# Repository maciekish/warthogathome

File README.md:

# Warthog at Home

This is a compilation of various resources to build an A-10C II cockpit for home entertainment. It is loosely based on [The Warthog Project](http://thewarthogproject.com) and frame designs by Flim on the ED forums.

This project started out as an idea for 3d-printed panels for the F-GT Lite racing chair, but as time went on it became more and more obvious that it's just too small and i would have to make way too many compromises along the way. For this reason i decided to use some of the available resources online to build a proper cockpit, but still trying to keep it as "stowable" as possible by making it modular and not mounted to the floor.

## License

This project is licensed under the MIT License except as stated otherwise in certain parts not made by me.

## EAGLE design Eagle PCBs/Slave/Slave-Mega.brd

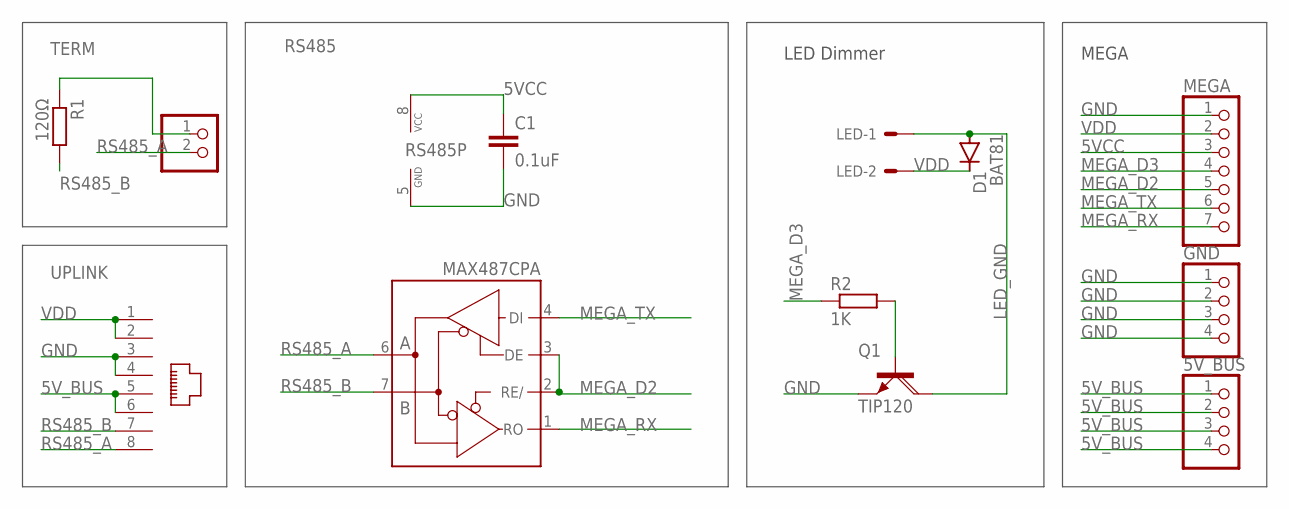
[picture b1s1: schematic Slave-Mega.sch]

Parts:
5V_BUS: PINHD-1X4; 1X04
C1: 0.1uF; C025-025X050
D1: BAT81; DO34-7
GND: PINHD-1X4; 1X04
LED: KK-156-2
MEGA: PINHD-1X7; 1X07
Q1: TIP120; TO220AH
R1: 120Ω; 0204/7
R2: 1K; 0207/10
RS485: MAX487CPA; DIL08
TERM: PINHD-1X2; 1X02
UPLINK: RJ45-8P8C

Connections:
5VCC: C1.1, MEGA.3, RS485.8 (VCC)
5V_BUS: 5V_BUS.1, 5V_BUS.2, 5V_BUS.3, 5V_BUS.4, UPLINK.5, UPLINK.6
GND: C1.2, GND.1, GND.2, GND.3, GND.4, MEGA.1, Q1.E, RS485.5 (GND), UPLINK.3, UPLINK.4
LED_GND: D1.A, LED.1, Q1.C
LED_PWM: Q1.B, R2.2
MEGA_D2: MEGA.5, RS485.2 (RE/), RS485.3 (DE)
MEGA_D3: MEGA.4, R2.1
MEGA_RX: MEGA.7, RS485.1 (RO)
MEGA_TX: MEGA.6, RS485.4 (DI)
RS485_A: RS485.6 (A), TERM.2, UPLINK.8
RS485_B: R1.2, RS485.7 (B), UPLINK.7
TERM: R1.1, TERM.1
VDD: D1.C, LED.2, MEGA.2, UPLINK.1, UPLINK.2

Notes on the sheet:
LED Dimmer
MEGA

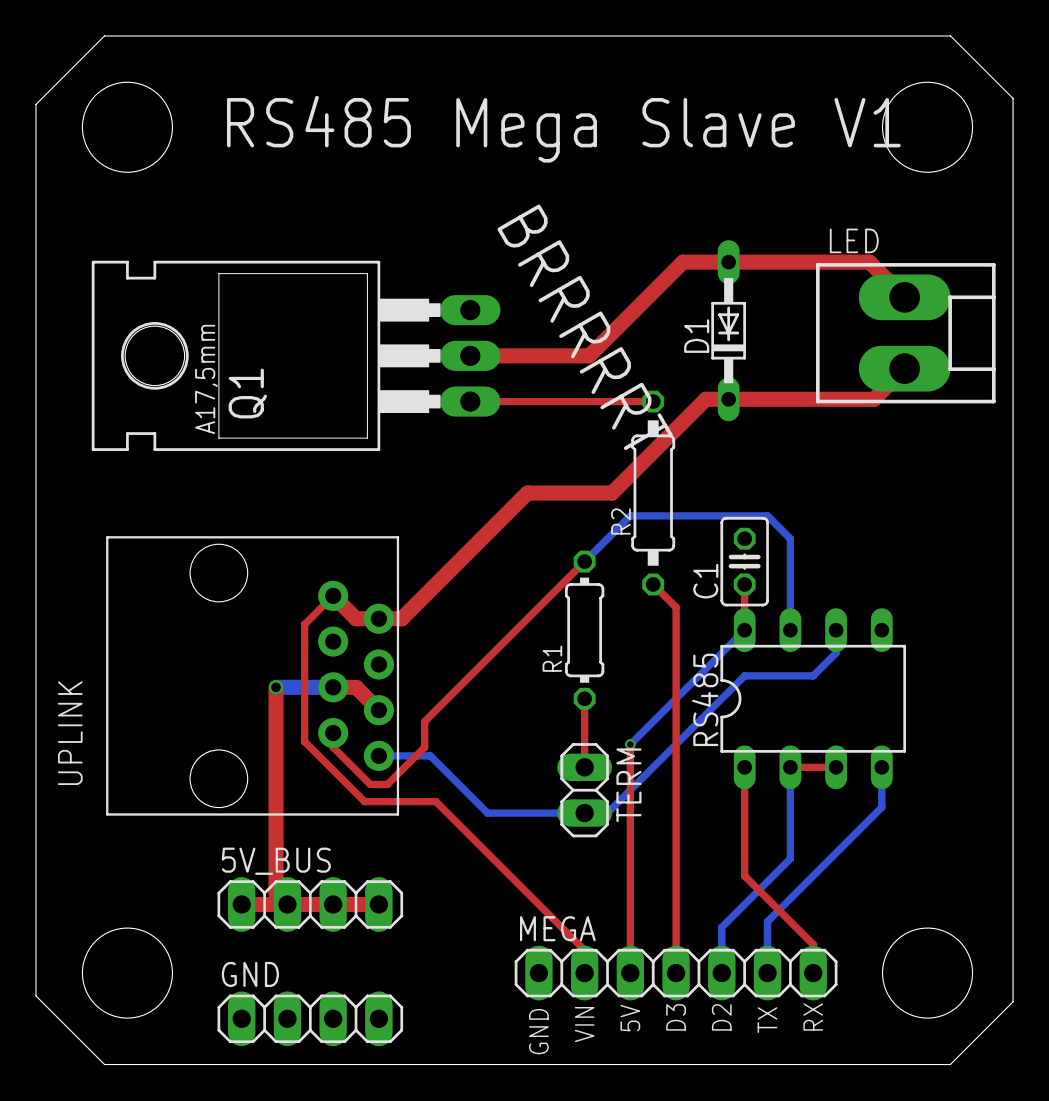
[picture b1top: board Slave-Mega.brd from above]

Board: 2 copper layers, 54.3 x 57.1 mm, 12 parts (0 on the bottom side), 13 nets.

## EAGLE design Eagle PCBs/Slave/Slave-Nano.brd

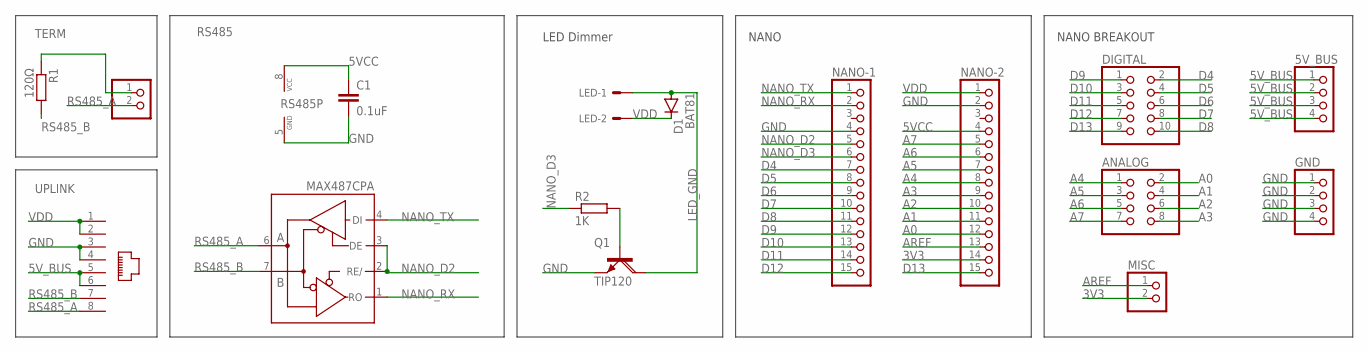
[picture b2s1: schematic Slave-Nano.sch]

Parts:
5V_BUS: PINHD-1X4; 1X04
ANALOG: PINHD-2X4; 2X04
C1: 0.1uF; C025-025X050
D1: BAT81; DO34-7
DIGITAL: PINHD-2X5; 2X05
GND: PINHD-1X4; 1X04
LED: KK-156-2
MISC: PINHD-1X2; 1X02
NANO-1, NANO-2: PINHD-1X15; 1X15
Q1: TIP120; TO220AH
R1: 120Ω; 0204/7
R2: 1K; 0204/7
RS485: MAX487CPA; DIL08
TERM: PINHD-1X2; 1X02
UPLINK: RJ45-8P8C

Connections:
3V3: MISC.2, NANO-2.14
5VCC: C1.1, NANO-2.4, RS485.8 (VCC)
5V_BUS: 5V_BUS.1, 5V_BUS.2, 5V_BUS.3, 5V_BUS.4, UPLINK.5, UPLINK.6
A0: ANALOG.2, NANO-2.12
A1: ANALOG.4, NANO-2.11
A2: ANALOG.6, NANO-2.10
A3: ANALOG.8, NANO-2.9
A4: ANALOG.1, NANO-2.8
A5: ANALOG.3, NANO-2.7
A6: ANALOG.5, NANO-2.6
A7: ANALOG.7, NANO-2.5
AREF: MISC.1, NANO-2.13
D4: DIGITAL.2, NANO-1.7
D5: DIGITAL.4, NANO-1.8
D6: DIGITAL.6, NANO-1.9
D7: DIGITAL.8, NANO-1.10
D8: DIGITAL.10, NANO-1.11
D9: DIGITAL.1, NANO-1.12
D10: DIGITAL.3, NANO-1.13
D11: DIGITAL.5, NANO-1.14
D12: DIGITAL.7, NANO-1.15
D13: DIGITAL.9, NANO-2.15
GND: C1.2, GND.1, GND.2, GND.3, GND.4, NANO-1.4, NANO-2.2, Q1.E, RS485.5 (GND), UPLINK.3, UPLINK.4
LED_GND: D1.A, LED.1, Q1.C
LED_PWM: Q1.B, R2.2
NANO_D2: NANO-1.5, RS485.2 (RE/), RS485.3 (DE)
NANO_D3: NANO-1.6, R2.1
NANO_RX: NANO-1.2, RS485.1 (RO)
NANO_TX: NANO-1.1, RS485.4 (DI)
RS485_A: RS485.6 (A), TERM.2, UPLINK.8
RS485_B: R1.2, RS485.7 (B), UPLINK.7
TERM: R1.1, TERM.1
VDD: D1.C, LED.2, NANO-2.1, UPLINK.1, UPLINK.2

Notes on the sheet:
LED Dimmer
NANO
NANO BREAKOUT

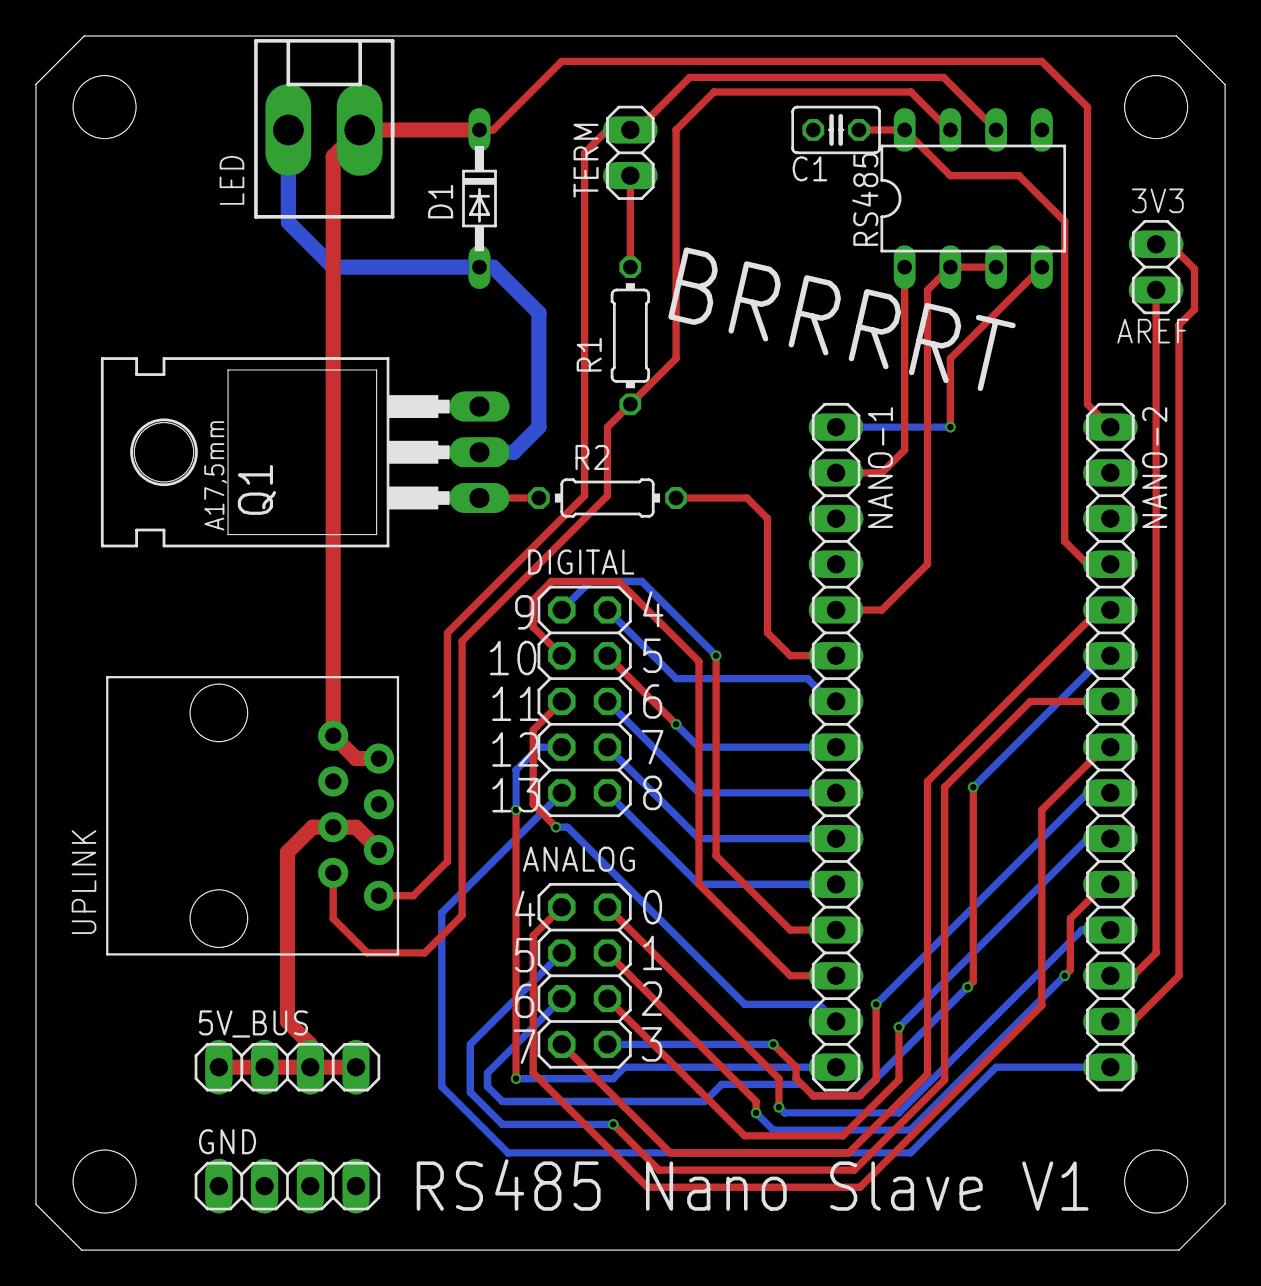
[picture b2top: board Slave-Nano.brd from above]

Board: 2 copper layers, 66.1 x 67.5 mm, 16 parts (0 on the bottom side), 33 nets.

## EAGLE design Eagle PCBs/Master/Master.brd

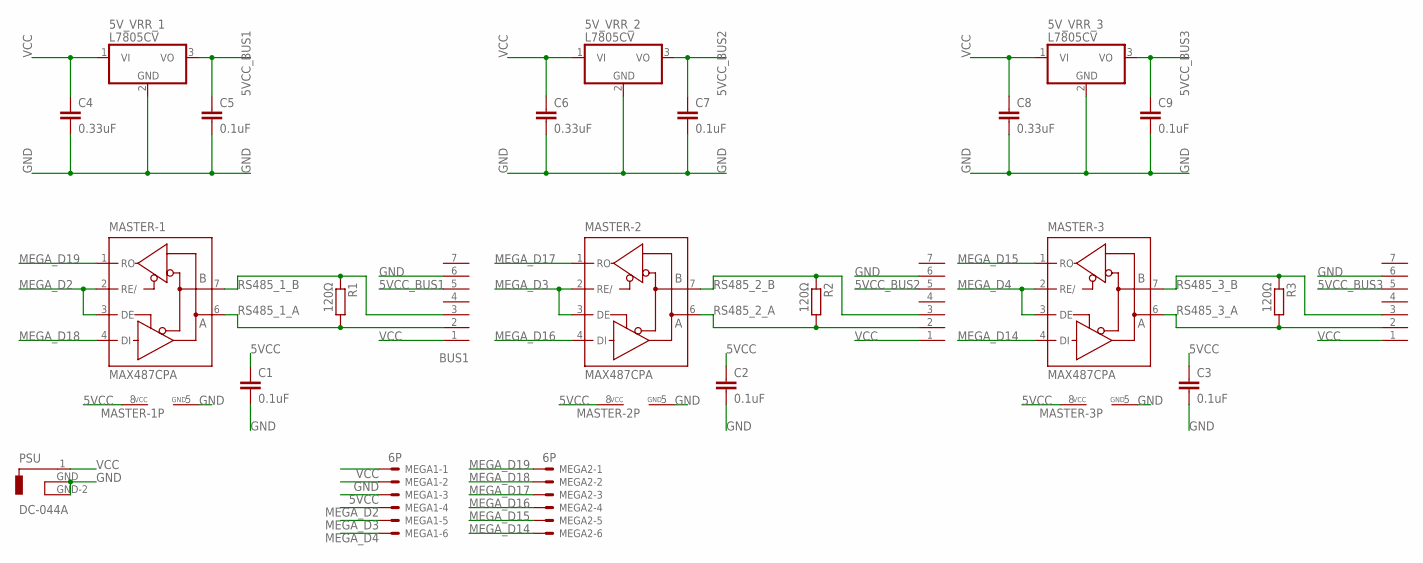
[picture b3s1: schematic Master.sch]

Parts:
5V_VRR_1, 5V_VRR_2, 5V_VRR_3: L7805CV; TO220H
BUS1, BUS2, BUS3: GX12-7P
C1, C2, C3, C5, C7, C9: 0.1uF; C025-025X050
C4, C6, C8: 0.33uF; C025-025X050
MASTER-1, MASTER-2, MASTER-3: MAX487CPA; DIL08
MEGA1, MEGA2: 6P; 22-23-2061
PSU: DC-044A
R1, R2, R3: 120Ω; 0207/10

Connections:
5VCC: C1.1, C2.1, C3.1, MASTER-1.8 (VCC), MASTER-2.8 (VCC), MASTER-3.8 (VCC), MEGA1.3
5VCC_BUS1: 5V_VRR_1.3 (VO), BUS1.5, C5.1
5VCC_BUS2: 5V_VRR_2.3 (VO), BUS2.5, C7.1
5VCC_BUS3: 5V_VRR_3.3 (VO), BUS3.5, C9.1
GND: 5V_VRR_1.2 (GND), 5V_VRR_2.2 (GND), 5V_VRR_3.2 (GND), BUS1.6, BUS2.6, BUS3.6, C1.2, C2.2, C3.2, C4.2, C5.2, C6.2, C7.2, C8.2, C9.2, MASTER-1.5 (GND), MASTER-2.5 (GND), MASTER-3.5 (GND), MEGA1.2, PSU.GND, PSU.GND-2
MEGA_D2: MASTER-1.2 (RE/), MASTER-1.3 (DE), MEGA1.4
MEGA_D3: MASTER-2.2 (RE/), MASTER-2.3 (DE), MEGA1.5
MEGA_D4: MASTER-3.2 (RE/), MASTER-3.3 (DE), MEGA1.6
MEGA_D14: MASTER-3.4 (DI), MEGA2.6
MEGA_D15: MASTER-3.1 (RO), MEGA2.5
MEGA_D16: MASTER-2.4 (DI), MEGA2.4
MEGA_D17: MASTER-2.1 (RO), MEGA2.3
MEGA_D18: MASTER-1.4 (DI), MEGA2.2
MEGA_D19: MASTER-1.1 (RO), MEGA2.1
RS485_1_A: BUS1.2, MASTER-1.6 (A), R1.2
RS485_1_B: BUS1.3, MASTER-1.7 (B), R1.1
RS485_2_A: BUS2.2, MASTER-2.6 (A), R2.2
RS485_2_B: BUS2.3, MASTER-2.7 (B), R2.1
RS485_3_A: BUS3.2, MASTER-3.6 (A), R3.2
RS485_3_B: BUS3.3, MASTER-3.7 (B), R3.1
VCC: 5V_VRR_1.1 (VI), 5V_VRR_2.1 (VI), 5V_VRR_3.1 (VI), BUS1.1, BUS2.1, BUS3.1, C4.1, C6.1, C8.1, MEGA1.1, PSU.1

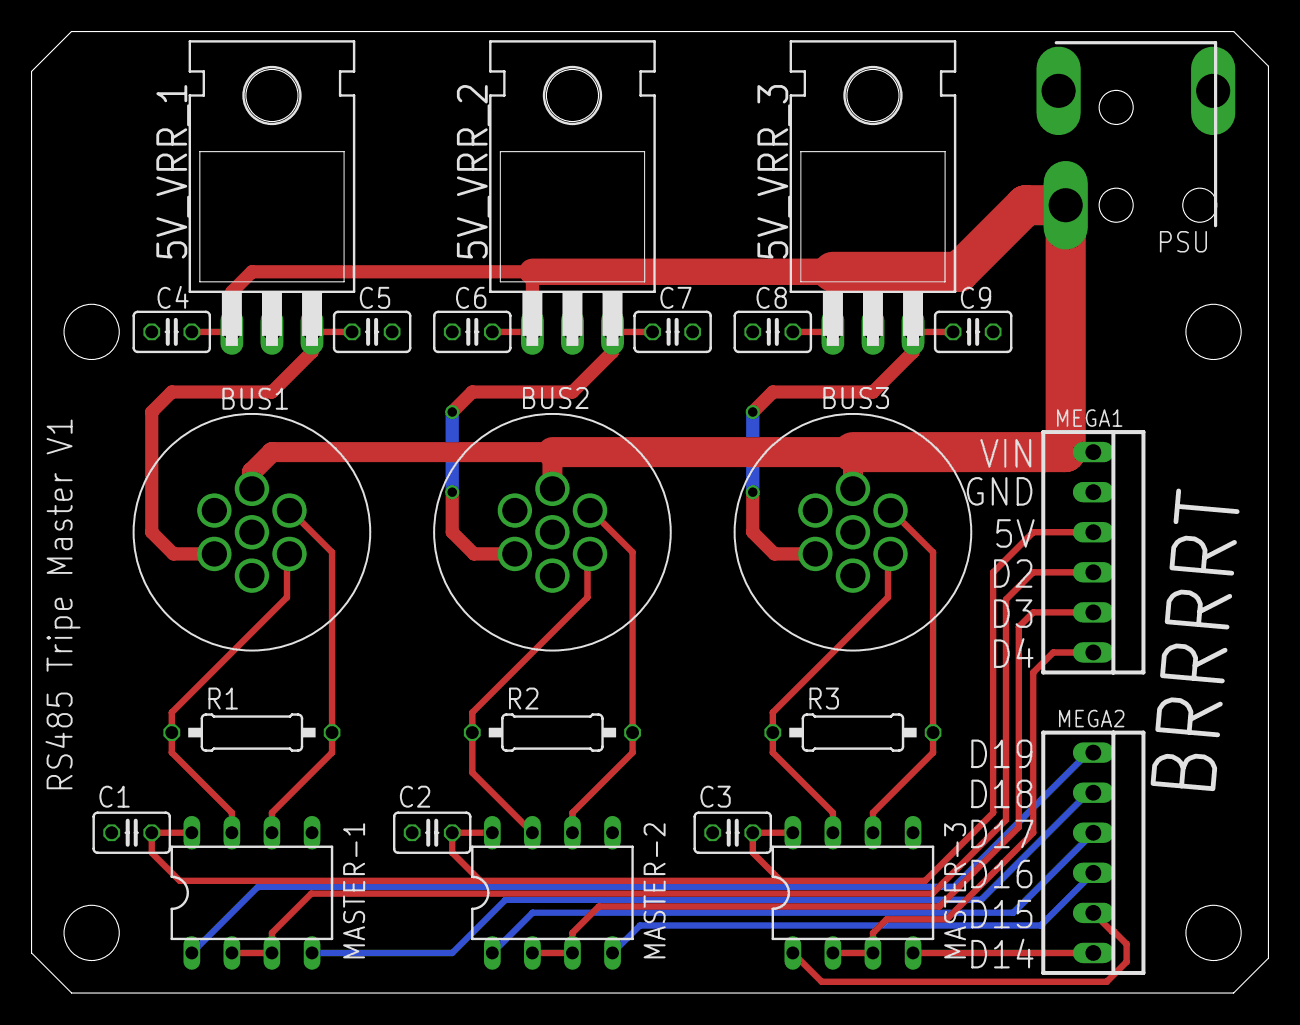
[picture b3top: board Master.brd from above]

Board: 2 copper layers, 78.4 x 61.0 mm, 24 parts (0 on the bottom side), 21 nets.

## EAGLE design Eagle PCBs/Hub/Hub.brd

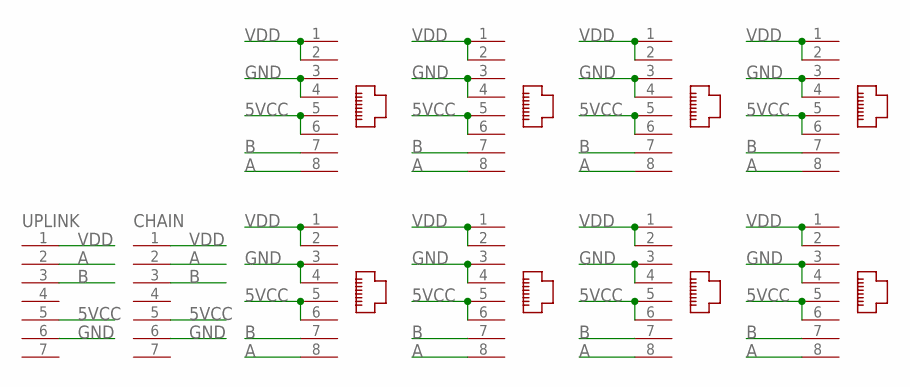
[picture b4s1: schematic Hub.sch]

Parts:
1, 2, 3, 4, 5, 6, 7, 8: RJ45-8P8C
CHAIN: GX12-7P
UPLINK: GX12-7P

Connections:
5VCC: 1.5, 1.6, 2.5, 2.6, 3.5, 3.6, 4.5, 4.6, 5.5, 5.6, 6.5, 6.6, 7.5, 7.6, 8.5, 8.6, CHAIN.5, UPLINK.5
A: 1.8, 2.8, 3.8, 4.8, 5.8, 6.8, 7.8, 8.8, CHAIN.2, UPLINK.2
B: 1.7, 2.7, 3.7, 4.7, 5.7, 6.7, 7.7, 8.7, CHAIN.3, UPLINK.3
GND: 1.3, 1.4, 2.3, 2.4, 3.3, 3.4, 4.3, 4.4, 5.3, 5.4, 6.3, 6.4, 7.3, 7.4, 8.3, 8.4, CHAIN.6, UPLINK.6
VDD: 1.1, 1.2, 2.1, 2.2, 3.1, 3.2, 4.1, 4.2, 5.1, 5.2, 6.1, 6.2, 7.1, 7.2, 8.1, 8.2, CHAIN.1, UPLINK.1

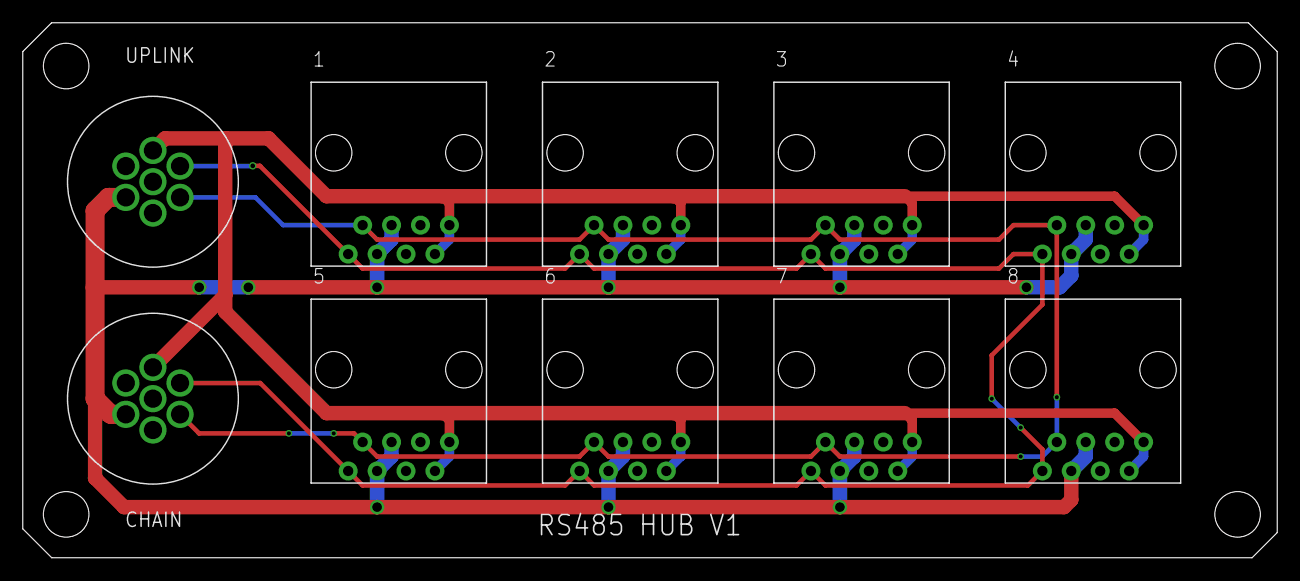
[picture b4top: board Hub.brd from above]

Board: 2 copper layers, 110.2 x 47.0 mm, 10 parts (0 on the bottom side), 5 nets.

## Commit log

2022-08-02 Minor PCB adjustments
2022-08-02 Modified some panels for LED strips
2022-08-03 Added a 5v bus to all PCBs
2022-08-05 Create VHF_I2C.ino
    Added a VHF OLED test sketch
2022-08-05 Updated poster
2022-08-08 Migrated Master PCB to KiCad
2022-08-08 Fixed mounting holes Added Mega pin labels
2022-08-08 Added a ground pour to top layer
2022-08-09 Modified mounting holes to M3
2022-08-09 Added Micro Blade fuse holder to each bus Updated cap 3d model Ignored KiCad backups
2022-08-09 Fixed library search paths
2022-08-11 Fixed 3d model
2022-08-11 Added power status LEDs to Master PCB
2022-08-11 Added power status LED to each bus
2022-08-11 DRC Excludions
2022-08-15 Master PCB Adjustments
2022-08-15 Updated Master PCB and completed first version of Hub
2022-08-16 Completed first version of Master Shield
2022-08-17 JLCPCB mappings wip
2022-08-17 Final Master Shield files
2022-08-17 Fixed J1 silkscreen
2022-08-17 Added RJ45 to lib
2022-08-18 Cleaned up libraries
2022-08-18 Fixed Master Shield 3D model paths
2022-08-18 Updated LCSC number for fuse
2022-08-18 First version of Hub completed
2022-08-18 Added some more silkscreen info to Hub
2022-08-18 Updated libraries for Arduino components
2022-08-19 Updated HUB LEDs
2022-08-19 Initial Slave Schematic
2022-08-19 Annotated Slave
2022-08-19 Added LED terminals
2022-08-19 Replaced 4P switch with 2x2P switches because of placement
2022-08-20 Slave PCB wip
2022-08-23 Slave WIP
2022-08-28 Tweaked Hub
2022-08-28 Generated Final Rev 1 files for Hub and Slave
2022-08-28 Fixed swapped LEDs on Slave
2022-08-28 Updated production files for Slave
2022-08-28 Updated TX/RX resistors to 1.8K
2022-08-28 Removed unnecessary resistor
2022-08-28 Include headers in BOM
2022-08-28 Added Mounting Holes to Slave PCB Added External Connection PCB
2022-08-29 Updated External Connectors BOM
2022-08-29 Updated .gitignore
2022-08-29 Remove ignored files
2022-08-29 Renamed Slave to Nano Slave
2022-08-29 Removed Eagle Libraries and Projects
2022-08-29 Mega Slave WIP
2022-08-31 4wire SPI OLED example
2022-08-31 Updated OLED SPI example to use hardware SPI on Arduino Nano
2022-09-01 Updated SPI example with hardware SPI for Arduino Mega
2022-09-01 Added switch to KiCad library
2022-09-02 Custom fonts for CMSP
2022-09-02 Improved CMSP font and drawing
2022-09-02 Added comment
2022-09-02 First 3.5" TFT Example
2022-09-04 Updated TFT display example
2022-09-04 TFT Example
2022-09-04 Updated TXT Example
2022-09-04 Completed CDU TFT Example
2022-09-07 Mega Slave Initial Routing
2022-09-07 Mega Slave Completed
2022-09-08 Initial version of the Nano Shield
2022-09-08 Finished Nano Shield
2022-09-11 Nano Slave Rev 2
2022-09-11 Modified Courtyard
2022-09-11 Mega Shield WIP
2022-09-11 Updated some silkscreen
2022-09-11 Added measurements to silkscreen
2022-09-11 Fixed PCB size
2022-09-12 Cleaned up routing on Nano Shield
2022-09-13 Added backlight control to TFT via hardware mod
2022-09-13 First version of ELEC PWR sketch
2022-09-19 Rearranged files
2022-09-19 Mega Slave Rev. 2 Completed
2022-09-22 Code cleanup
2022-09-22 Completed panels for right column of right console
2022-10-01 Completed Caution Panel
2022-10-04 UFC WIP
2022-10-10 Added Laser Calibration Files
2022-10-10 UFC Completed
2022-10-12 Updated PCB production files
2022-10-13 Fixed part number of screw terminals
2022-10-19 Use 1/4 duty cycle for backlight
2022-11-03 Nano SFF Slave
2022-11-07 Cleaned up PCB
2022-11-07 Mega SFF Slave WIP
2022-11-11 Mega SFF WIP
2022-11-12 Mega SFF Slave Rev. 1
2022-11-12 Nano SFF Rev. 1
2022-11-14 Misc files
2022-12-01 Updated production files
2022-12-01 3D Models & Oxygen Regulator code WIP
2022-12-01 Fixed terminal part number
2022-12-01 Fixed silkscreen
2022-12-04 Updated Nano SFF Slave RS485 Switch and Silkscreen
2022-12-04 Updated Mega SFF Slave RS485 Switch and Silkscreen
2022-12-04 Improved Nano SFF Silkscreen
2022-12-05 Added fuse models
2022-12-05 Micro SFF Slave WIP
2022-12-09 Simulation
2022-12-09 Nano SFF with DS4560S-AR+ hotplug protection (Not Orderable)
2022-12-09 Added a drain resistor and updated component values
2022-12-09 Added new components
2022-12-15 Nano SFF With Hotplug and RS485 Protection
2022-12-15 Added Hotplug and RS485 protection to Mega SFF Schematic. PCB to go
2022-12-15 Fixed silkscreen on Nano SFF
2022-12-15 Added Hotplug and RS485 protection to Mega SFF. Capacitor LCSC numbers to go.
2022-12-15 Updated LCSC number and size of voltage ramp capacitors for Nano SFF Slave
2022-12-15 Updated LCSC number and size of voltage ramp capacitors for Mega SFF Slave
2022-12-16 Added Caution Panel and panelized 3 panels for production
2022-12-16 Added a top cover for the Caution Panel
2022-12-16 Added checklists
2022-12-16 Added more checklists
2022-12-19 Oxygen Regulator Sketch
2022-12-21 Updated panelized files
2022-12-26 Updated micro-fit pinout for more power
2022-12-26 Updated hub pinout for more power
2022-12-29 Updated Nano SFF Slave for correct block terminal size
2022-12-29 Regenerated production files
2022-12-29 Updated Mega SFF Slave for correct terminal block size
2022-12-29 Updated Nano SFF Revision and date information
2022-12-31 Master WIP
2023-01-01 Added 1 pos dip switch
2023-01-02 Master Rev. 1
2023-01-02 Updated Master Silkscreen
2023-01-02 Tweaked Groundplane Size
2023-01-03 Updated Master to use PCIe Power Directly
2023-01-03 Added Spring Terminals
2023-01-09 Updated HUB
2023-01-09 Removed voltage ramp and some protection from Nano SFF Slave
2023-01-09 Updated Nano SFF Slave
2023-01-11 Arduino Code for Lighting Panel
